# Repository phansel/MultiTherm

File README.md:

# MultiTherm
This repository contains the hardware, firmware, and drivers for MultiTherm.

MultiTherm allows you to log data from a few [tiny I2C temperature sensors](https://www.ti.com/lit/ds/symlink/tmp117.pdf) via your computer's USB port. A few could range from 1-4 or more.

Each temperature sensor is on a flexible 200mm probe ribbon; route them in free space however you like, or even trim their ribbons to length. An adhesive sticker provides thermal coupling to your device under test.

MultiTherm can be used as a lower-cost substitute for a resistance temperature detector (RTD) and data acquisition interface (DAQ) while still featuring NIST-traceable calibration accurate within ±0.1°C (between –20°C to 50°C) and 0.0078°C read-out resolution.

Working temperature range is –55 °C to 150 °C.

MultiTherm will be made available for purchase at a later date.

## Applications
- Optical bench temperature compensation
- Bulk material conductivity measurement
- Power electronics testing and characterization
- Chemical synthesis
- Bioreactors, polymerase chain reaction
- Wearable devices

## Project structure
- ESP32C6 firmware: [mt-fw](./mt-fw)
- PCB design files: [mt-hw](./mt-hw)
- Userspace serial-to-npyz driver: [mt-relay](./mt-relay)
- Project roadmap: [ROADMAP.md](./ROADMAP.md)

## License
[GPLv3](./LICENSE)

## Copyright
[Paul Hansel](https://paulhansel.com), 2024

## Thanks to:
- [Rust on ESP community](https://github.com/esp-rs)
- [KiCAD developers](https://www.kicad.org/sponsors/sponsors/)
- [Rust Embedded Working Group](https://blog.rust-embedded.org/)

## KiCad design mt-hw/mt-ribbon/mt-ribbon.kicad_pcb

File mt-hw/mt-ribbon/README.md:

# MultiTherm Ribbon

Individual ribbon cable flex PCB with temperature probe on the end.

Device address is configurable via solderable jumpers.

Supports WSON-6 (TMP117xxDRV) and DSBGA (TMP117xxYBG) packages. Populate one.

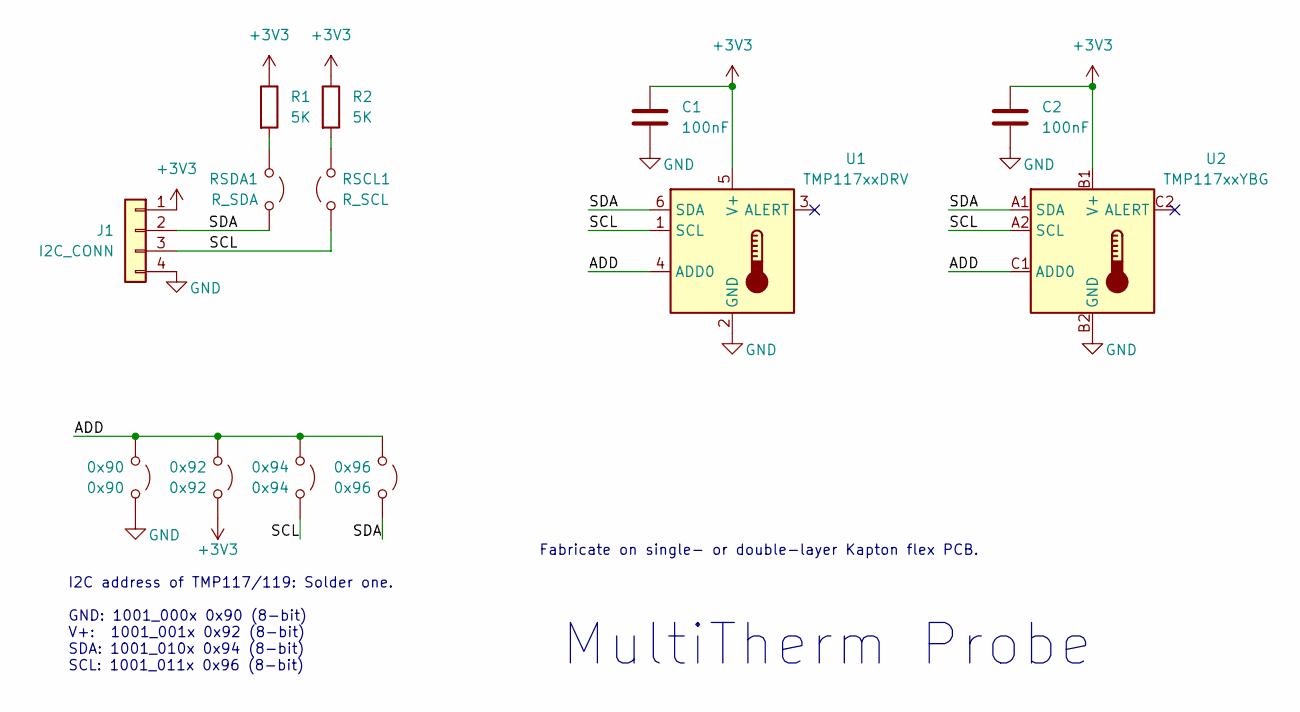
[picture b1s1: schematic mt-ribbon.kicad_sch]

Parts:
0x90: 0x90; SolderJumper-2_P0.43mm_Open_Pad0.3x0.75mm
0x92: 0x92; SolderJumper-2_P0.43mm_Open_Pad0.3x0.75mm
0x94: 0x94; SolderJumper-2_P0.43mm_Open_Pad0.3x0.75mm
0x96: 0x96; SolderJumper-2_P0.43mm_Open_Pad0.3x0.75mm
C1, C2: 100nF; C_0402_1005Metric
J1: I2C_CONN; PinHeader_1x04_P2.54mm_Vertical
R1, R2: 5K; R_0402_1005Metric_Pad0.72x0.64mm_HandSolder
RSCL1: R_SCL; SolderJumper-2_P0.43mm_Open_Pad0.3x0.75mm
RSDA1: R_SDA; SolderJumper-2_P0.43mm_Open_Pad0.3x0.75mm
U1: TMP117xxDRV; WSON-6-1EP_2x2mm_P0.65mm_EP1x1.6mm
U2: TMP117xxYBG; Texas_DSBGA-6_0.95x1.488mm_Layout2x3_P0.4mm

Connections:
+3V3: 0x92.1 (A), C1.1, C2.1, J1.1, R1.1, R2.1, U1.5 (V+), U2.B1 (V+)
/ADD: 0x90.2 (B), 0x92.2 (B), 0x94.2 (B), 0x96.2 (B), U1.4 (ADD0), U2.C1 (ADD0)
/SCL: 0x94.1 (A), J1.3, RSCL1.1 (A), U1.1 (SCL), U2.A2 (SCL)
/SDA: 0x96.1 (A), J1.2, RSDA1.1 (A), U1.6 (SDA), U2.A1 (SDA)
GND: 0x90.1 (A), C1.2, C2.2, J1.4, U1.2 (GND), U2.B2 (GND)
unnamed: R2.2, RSCL1.2 (B)
unnamed: R1.2, RSDA1.2 (B)

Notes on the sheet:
I2C address of TMP117/119: Solder one. GND: 1001_000x 0x90 (8-bit) V+: 1001_001x 0x92 (8-bit) SDA: 1001_010x 0x94 (8-bit) SCL: 1001_011x 0x96 (8-bit)
Fabricate on single- or double-layer Kapton flex PCB.
MultiTherm Probe

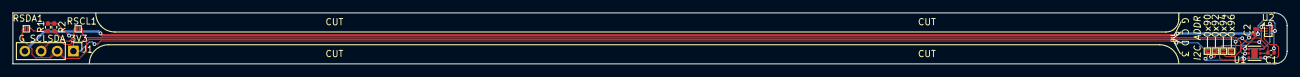
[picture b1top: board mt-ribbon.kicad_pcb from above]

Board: 2 copper layers, 200.0 x 8.0 mm, 13 parts (0 on the bottom side), 7 nets.

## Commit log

2024-11-13 Initial multitherm commit
2024-11-13 Update README and gitignore
2024-11-13 Update rust.yml
    Install libudev-dev
2024-11-14 Add image of ribbon PCB

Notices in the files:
mt-hw/mt-ribbon/mt-ribbon.kicad_pcb:
Paul Hansel Copyright 2024
